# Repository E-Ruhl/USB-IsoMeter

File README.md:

# USB-IsoMeter

The goal of this project is to develop a USB isolator that can power and transmit date through usb from one device to another while offering protection and power monitoring of the output port, displaying Voltage and Current as well as providing Power and energy metering. Basically the designe will be intended to protect a more expensive control/coding device from a potentially janky test device with the added benifit of providing some generic data read outs for said test device. 

This project was originally inspiered by the work of Oliver, who's work I will attempt to link here later.

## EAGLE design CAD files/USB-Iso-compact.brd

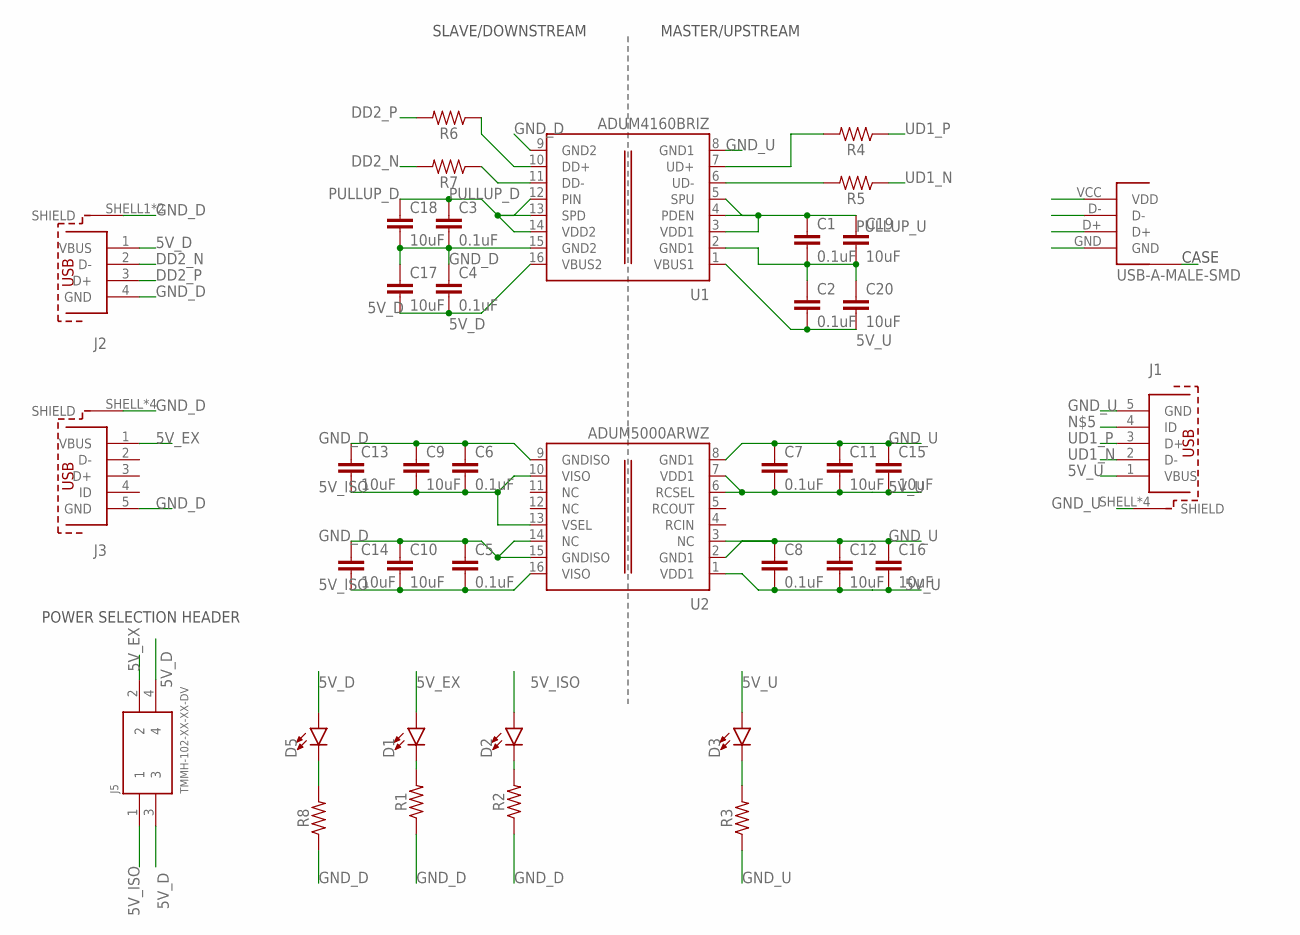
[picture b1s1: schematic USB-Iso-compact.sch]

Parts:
C1, C2, C3, C4, C5, C6, C7, C8: 0.1uF; 0603
C9, C10, C11, C12, C13, C14, C15, C16, C17, C18, C19, C20: 10uF; 0603
D1, D2, D3, D5: LED0603; LED-0603
J1, J3: MICRO-USB-SOCKET; 629105136821
J2: USB-A-FEMALE-SMD; 629104151021
J4: USB-A-MALE-SMD
J5: TMMH-102-XX-XX-DV
R1, R2, R3, R4, R5, R6, R7, R8: 0603
U1: ADUM4160BRIZ; SO-16W
U2: ADUM5000ARWZ; SO-16W

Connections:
5V_D: C4.2, C17.2, D5.A, J2.1 (VBUS), J5.3, J5.4, U1.16 (VBUS2)
5V_EX: D1.A, J3.1 (VBUS), J5.2
5V_ISO: C5.2, C6.2, C9.2, C10.2, C13.2, C14.2, D2.A, J5.1, U2.10 (VISO), U2.13 (VSEL), U2.16 (VISO)
5V_U: C2.2, C7.2, C8.2, C11.2, C12.2, C15.2, C16.2, C20.2, D3.A, J1.1 (VBUS), J4.VCC (VDD), U1.1 (VBUS1), U2.1 (VDD1), U2.6 (RCSEL), U2.7 (VDD1)
DD1_N: R7.1, U1.11 (DD-)
DD1_P: R6.1, U1.10 (DD+)
DD2_N: J2.2 (D-), R7.2
DD2_P: J2.3 (D+), R6.2
GND_D: C3.2, C4.1, C5.1, C6.1, C9.1, C10.1, C13.1, C14.1, C17.1, C18.2, J2.4 (GND), J2.SHELL1 (SHIELD), J2.SHELL2 (SHIELD), J3.5 (GND), J3.SHELL (SHIELD), J3.SHELL1 (SHIELD), J3.SHELL2 (SHIELD), J3.SHELL3 (SHIELD), R1.1, R2.1, R8.1, U1.9 (GND2), U1.15 (GND2), U2.9 (GNDISO), U2.14 (NC), U2.15 (GNDISO)
GND_U: C1.2, C2.1, C7.1, C8.1, C11.1, C12.1, C15.1, C16.1, C19.2, C20.1, J1.5 (GND), J1.SHELL (SHIELD), J1.SHELL1 (SHIELD), J1.SHELL2 (SHIELD), J1.SHELL3 (SHIELD), J4.CASE1 (CASE), J4.CASE2 (CASE), J4.GND, R3.1, U1.2 (GND1), U1.8 (GND1), U2.2 (GND1), U2.3 (NC), U2.8 (GND1)
unnamed: D5.C, R8.2
unnamed: D1.C, R1.2
unnamed: D2.C, R2.2
unnamed: D3.C, R3.2
PULLUP_D: C3.1, C18.1, U1.12 (PIN), U1.13 (SPD), U1.14 (VDD2)
PULLUP_U: C1.1, C19.1, U1.3 (VDD1), U1.4 (PDEN), U1.5 (SPU)
UD1_N: J1.2 (D-), J4.D-, R5.1
UD1_P: J1.3 (D+), J4.D+, R4.1
UD2_N: R5.2, U1.6 (UD-)
UD2_P: R4.2, U1.7 (UD+)

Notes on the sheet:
MASTER/UPSTREAM
SLAVE/DOWNSTREAM
POWER SELECTION HEADER

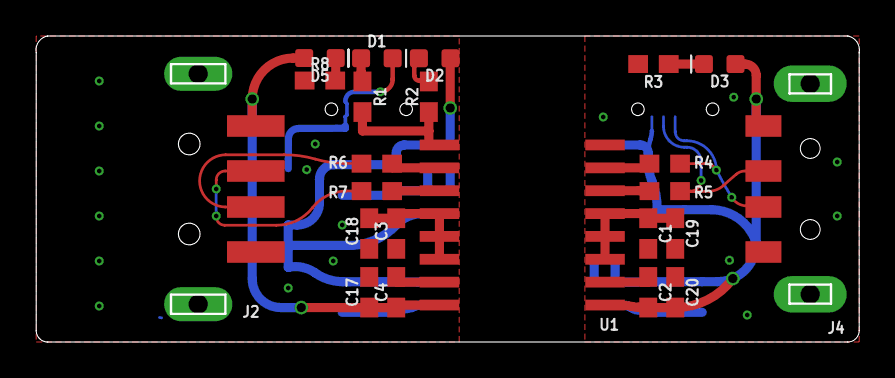
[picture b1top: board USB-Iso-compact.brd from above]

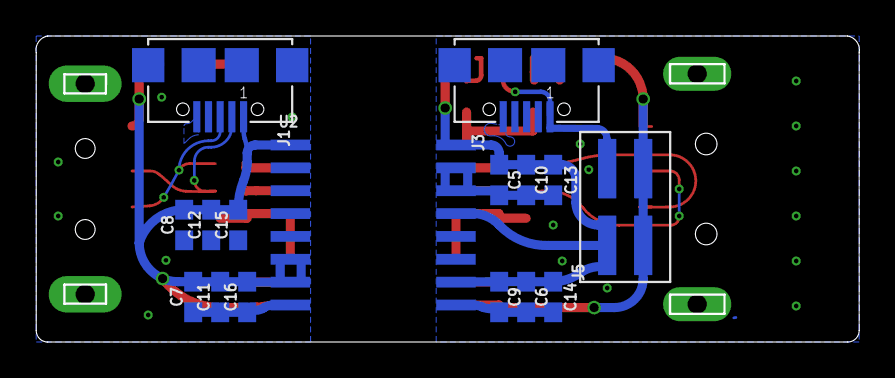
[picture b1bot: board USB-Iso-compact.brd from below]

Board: 2 copper layers, 45.6 x 16.9 mm, 39 parts (16 on the bottom side), 20 nets.

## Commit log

2018-07-02 Original and Compact design'

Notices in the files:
parts and their libraries:
SparkFun-Capacitors: Licensing: Creative Commons ShareAlike 4.0 International - https://creativecommons.org/licenses/by-sa/4.0
